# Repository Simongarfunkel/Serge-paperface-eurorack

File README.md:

# Serge Paperface → Eurorack

Modulfamilie: die Serge-Paperface-Module (73-75-Schaltungen) als Eurorack-Module.
Jedes Modul bekommt einen eigenen Ordner unter `modules/` mit Hardware-Revisionen, Panel und Dokumentation.
Gemeinsame Vorgaben stehen in [`docs/konventionen.md`](docs/konventionen.md).

## Module

| Modul | Ordner | Stand | Fertigungsfreigabe |
|---|---|---|---|
| Envelope | [`modules/envelope`](modules/envelope) | REV1: KiCad-Projekt komplett geroutet, ERC/DRC 0 Meldungen | nein – mechanische Prüfung und Prototyp offen |
| VCO (Oszillator) | [`modules/vco`](modules/vco) | REV1: KiCad-Schaltplan vollständig, Platine platziert, noch unverdrahtet, ERC/DRC offen | nein |
| Triple Waveshaper, Peak/Trough, Comparator, Dual Processor, Gate, Ring, Reverb, Preamp, Positive/Negative Slew | `modules/<modul>` | Originalauszüge abgelegt, noch kein KiCad | nein |

Neue Module: [`modules/_vorlage`](modules/_vorlage) kopieren und umbenennen. Bauteilwahl: [`docs/bauteilregel.md`](docs/bauteilregel.md). Gemeinsame KiCad-Bibliotheken: [`shared/kicad`](shared/kicad).

## Weitere Inhalte

- [`system/panel-layout`](system/panel-layout) – Gesamt-Panel-Layout (Vectorworks + PDF-Export).

## Lizenz

Noch nicht festgelegt. Die Schaltungen beruhen auf den Serge-73-75-Build-Unterlagen; deren Rechte liegen bei den
jeweiligen Urhebern. Auszüge aus den Originalunterlagen nicht ohne Klärung öffentlich stellen.
Fremdbibliotheken behalten ihre Lizenz (z. B. `LICENSE_AudioJacks.txt`, MIT, im Envelope-Projekt).

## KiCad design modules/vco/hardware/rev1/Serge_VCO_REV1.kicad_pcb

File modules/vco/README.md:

# VCO (Oszillator)

**Stand:** REV1 KiCad-Entwurf (22.10.2026), unverdrahtet, ERC/DRC offen · **Freigabe:** nein

## Dokumente

- [`docs/Serge_73-75_VCO_Originalauszug.pdf`](docs/Serge_73-75_VCO_Originalauszug.pdf) – Originalschaltung, BOM, Trimmanleitung.
- [`docs/Schaltplan_Original.png`](docs/Schaltplan_Original.png) – Originalschaltplan als Bild (300 dpi, gedreht).
- [`docs/Serge_VCO_Stabilisierung_Gruen.pdf`](docs/Serge_VCO_Stabilisierung_Gruen.pdf) – Stabilisierungsvorschlag (16.10.2026, Entwurf, keine freigegebene Nachbauschaltung).

## Original (Kurzfassung)

LM3900-Kern, 3 × 2N3904, 27-nF-Zeitkondensator, drei Trimmer:
1. Initial Offset – tiefste Frequenz, etwa 5–10 Hz
2. Range – Spanne bis etwa 10–14 kHz
3. Sinusformung im Saw-zu-Sinus-Waveshaper

## Geplante Änderungen (laut Vorschlag)

- Konkret: 27 nF als Folie oder C0G/NP0, 100 nF Entkopplung LM3900 Pin 14/7, kurze Timing-Schleife.
- Neu auszulegen: 1-V/Okt.-Eingang mit gepaartem NPN-Expo, Referenzstromregelung, Tempco, gepufferte Präzisionsreferenz.
- Ziel: fünf Oktaven, ±5 Cent nach Warmlaufen – noch nicht nachgewiesen.

## Revisionen

| Rev | Ordner | Inhalt | Status |
|---|---|---|---|
| REV1 | [`hardware/rev1`](hardware/rev1) | KiCad-Schaltplan (Label-Netzliste), Platine platziert, Stückliste, Netzliste | Entwurf – vor dem Öffnen [`BITTE_ZUERST_LESEN_REV1.txt`](hardware/rev1/BITTE_ZUERST_LESEN_REV1.txt) |

## Nächste Schritte

1. ERC in KiCad, Routing (Freerouting), DRC.
2. Abweichung SUM_P/SH_IN gegen Originalquelle prüfen (siehe BITTE_ZUERST_LESEN).
3. Originalkern aufbauen, Strom-/Spannungsbereiche und Reset-Zeit messen.

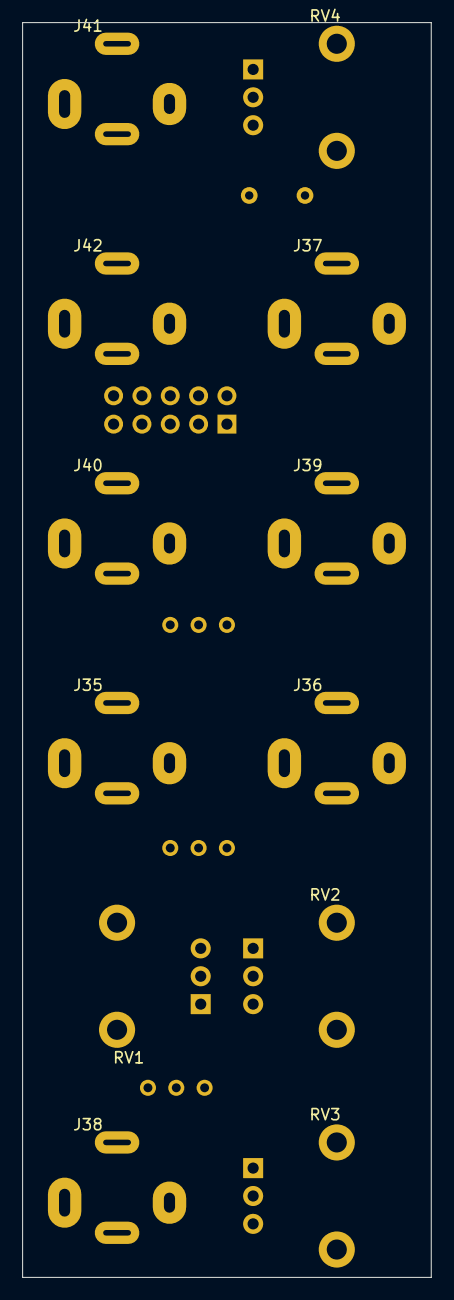
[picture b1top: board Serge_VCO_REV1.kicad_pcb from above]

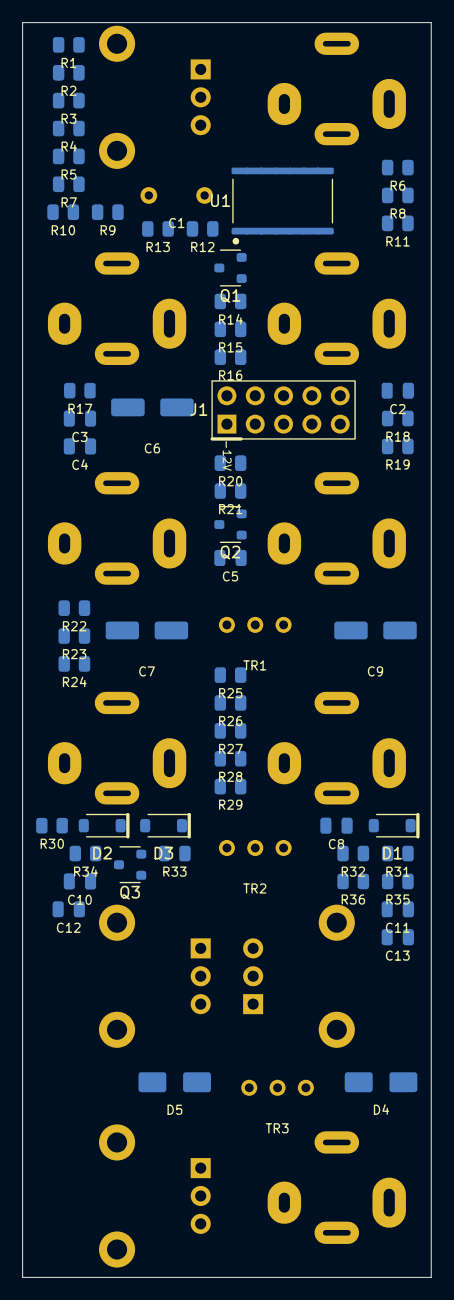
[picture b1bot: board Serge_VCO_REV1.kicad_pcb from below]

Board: 2 copper layers, 36.6 x 112.5 mm, 74 parts (62 on the bottom side), 46 nets, no tracks yet.

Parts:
C1: 27n Folie; C_Rect_L7.2mm_W2.5mm_P5.00mm
C2: 33p; C_0805_2012Metric
C3: 47p; C_0805_2012Metric
C4: 10n; C_0805_2012Metric
C5, C8: 82p; C_0805_2012Metric
C6, C9: 47u; CP_Elec_5x5.4
C7: 4u7; CP_Elec_5x5.4
C10, C11: 10u X7R; C_0805_2012Metric
C12, C13: 100n; C_0805_2012Metric
D1, D2, D3: 1N4148W; D_SOD-123
D4, D5: SS14; D_SMA
J1: EURORACK 10-PIN; PinHeader_2x05_P2.54mm_Vertical
J35: VC1 / PJ301BM; Jack_3.5mm_QingPu_WQP-PJ301BM_Vertical
J36: VC2 / PJ301BM; Jack_3.5mm_QingPu_WQP-PJ301BM_Vertical
J37: WAVE SHAPE CV / PJ301BM; Jack_3.5mm_QingPu_WQP-PJ301BM_Vertical
J38: SYNC / PJ301BM; Jack_3.5mm_QingPu_WQP-PJ301BM_Vertical
J39: SAW OUT / PJ301BM; Jack_3.5mm_QingPu_WQP-PJ301BM_Vertical
J40: SAW AC OUT / PJ301BM; Jack_3.5mm_QingPu_WQP-PJ301BM_Vertical
J41: SINE OUT / PJ301BM; Jack_3.5mm_QingPu_WQP-PJ301BM_Vertical
J42: SINE AC OUT / PJ301BM; Jack_3.5mm_QingPu_WQP-PJ301BM_Vertical
Q1, Q2, Q3: MMBT3904; SOT-23_EBC_MMBT3904
R1: 3M3; R_0805_2012Metric
R2, R3, R6, R7, R20, R28: 22k; R_0805_2012Metric
R4, R5, R8, R9, R25: 330k; R_0805_2012Metric
R10, R11: 1M; R_0805_2012Metric
R12: 15k; R_0805_2012Metric
R13, R15: 3k3; R_0805_2012Metric
R14: 15; R_0805_2012Metric
R16, R31: 33k; R_0805_2012Metric
R17, R26, R34: 1k; R_0805_2012Metric
R18: 82k; R_0805_2012Metric
R19: 4k7; R_0805_2012Metric
R21, R23, R33, R35: 330; R_0805_2012Metric
R22: 2k2; R_0805_2012Metric
R24, R36: 100k; R_0805_2012Metric
R27: 4M7; R_0805_2012Metric
R29, R30: 1M5; R_0805_2012Metric
R32: 10k; R_0805_2012Metric
RV1, RV2: 25k linear; Potentiometer_Alpha_RD901F-40-00D_Single_Vertical_CircularH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
RV3: 25k linear FREQ; Potentiometer_Alpha_RD901F-40-00D_Single_Vertical_CircularH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
RV4: 25k linear WAVE SHAPE; Potentiometer_Alpha_RD901F-40-00D_Single_Vertical_CircularH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
TR1: 25k OFFSET; Potentiometer_Bourns_3296W_Vertical
TR2: 25k RANGE; Potentiometer_Bourns_3296W_Vertical
TR3: 25k SINE; Potentiometer_Bourns_3296W_Vertical
U1: LM3900M (SOIC); SOIC-14_3.9x8.7mm_P1.27mm

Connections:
/+12V: D4.2, J1.9, J1.10
/-12V: D5.1, J1.1, J1.2
/CMP_FB: C2.2, R17.1
/CMP_N: C3.2, R18.2, R19.2
/CMP_OUT: R15.2, R17.2
/CMP_P: C2.1, R16.2
/CV1_A: R2.1, R4.1, RV1.1
/CV1_B: R3.1, R5.1, RV1.3
/CV1_TIP: J35.T, R1.2, RV1.2
/CV2_A: R6.1, R8.1, RV2.1
/CV2_B: R7.1, R9.1, RV2.3
/CV2_TIP: J36.T, RV2.2
/FREQ_W: R10.1, RV3.2
/GND: C10.2, C11.1, C12.2, C13.1, J1.3, J1.4, J1.5, J1.6, J1.7, J1.8, J35.S, J35.TN, J36.S, J36.TN, J37.S, J37.TN, J38.S, J38.TN, J39.S, J40.S, J41.S, J42.S, R2.2, R3.2, R6.2, R7.2, R20.2, R24.2, R28.2, R32.2, R34.2, R36.2, RV3.1, RV4.1, TR1.1, TR3.3
/INT_N: C1.1, Q1.2
/NODE_X: R12.2, R13.2
/OFS_W: R11.1, TR1.2
/Q1_C: Q1.3, R15.1
/Q1_E: Q1.1, R14.1
/Q2_B: Q2.2, R21.2
/Q3_B: Q3.2, R33.2
/RANGE_W: C5.1, TR2.2
/SAW: C1.2, C3.1, R14.2, R16.1, R21.1
/SAW_AC: C6.2, J40.T, R24.1
/SAW_BUF: Q2.1, R22.1, R23.1, TR2.1, TR3.1
/SAW_OUT: C6.1, J39.T, R23.2
/SH_FB: C8.2, D2.2, R31.2, R32.1
/SH_IN: D3.2, R25.2, R27.2, R29.2
/SH_N: C8.1, D2.1, D3.1, R30.1
/SH_OUT: R30.2, R31.1, R33.1
/SINE_AC: C9.2, J42.T, R36.1
/SINE_AC_IN: C7.1, R25.1
/SINE_BUF: Q3.1, R34.1, R35.1
/SINE_OUT: C9.1, J41.T, R35.2
/SINE_W: C7.2, TR3.2
/SUM_N: R4.2, R8.2, R10.2, R12.1, U1.6
/SUM_P: C5.2, R5.2, R9.2, R11.2, U1.1
/SYNC_AC: C4.2, R19.1
/SYNC_IN: C4.1, J38.T, R20.1
/U1A_OUT: R13.1, U1.5
/V+: C10.1, C12.1, D4.1, Q2.3, Q3.3, R1.1, R18.1, R26.1, RV3.3, TR1.3
/V-: C11.2, C13.2, D5.2, R22.2, TR2.3
/WS_D: D1.1, R29.1
/WS_IN: D1.2, J37.T, R28.1
/WS_TOP: R26.2, RV4.3
/WS_W: R27.1, RV4.2

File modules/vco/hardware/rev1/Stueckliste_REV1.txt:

Serge VCO REV1 - Stueckliste (abgeleitet aus dem Schaltplan)
Ref	Wert	Footprint	Ausfuehrung
C1	27n Folie	C_Rect_L7.2mm_W2.5mm_P5.00mm	THT
C2	33p	C_0805_2012Metric	SMD
C3	47p	C_0805_2012Metric	SMD
C4	10n	C_0805_2012Metric	SMD
C5	82p	C_0805_2012Metric	SMD
C6	47u	CP_Elec_5x5.4	SMD
C7	4u7	CP_Elec_5x5.4	SMD
C8	82p	C_0805_2012Metric	SMD
C9	47u	CP_Elec_5x5.4	SMD
C10	10u X7R	C_0805_2012Metric	SMD
C11	10u X7R	C_0805_2012Metric	SMD
C12	100n	C_0805_2012Metric	SMD
C13	100n	C_0805_2012Metric	SMD
D1	1N4148W	D_SOD-123	SMD
D2	1N4148W	D_SOD-123	SMD
D3	1N4148W	D_SOD-123	SMD
D4	SS14	D_SMA	SMD
D5	SS14	D_SMA	SMD
J1	EURORACK 10-PIN	PinHeader_2x05_P2.54mm_Vertical	THT
J35	VC1 / PJ301BM	Jack_3.5mm_QingPu_WQP-PJ301BM_Vertical	THT
J36	VC2 / PJ301BM	Jack_3.5mm_QingPu_WQP-PJ301BM_Vertical	THT
J37	WAVE SHAPE CV / PJ301BM	Jack_3.5mm_QingPu_WQP-PJ301BM_Vertical	THT
J38	SYNC / PJ301BM	Jack_3.5mm_QingPu_WQP-PJ301BM_Vertical	THT
J39	SAW OUT / PJ301BM	Jack_3.5mm_QingPu_WQP-PJ301BM_Vertical	THT
J40	SAW AC OUT / PJ301BM	Jack_3.5mm_QingPu_WQP-PJ301BM_Vertical	THT
J41	SINE OUT / PJ301BM	Jack_3.5mm_QingPu_WQP-PJ301BM_Vertical	THT
J42	SINE AC OUT / PJ301BM	Jack_3.5mm_QingPu_WQP-PJ301BM_Vertical	THT
Q1	MMBT3904	SOT-23_EBC_MMBT3904	SMD
Q2	MMBT3904	SOT-23_EBC_MMBT3904	SMD
Q3	MMBT3904	SOT-23_EBC_MMBT3904	SMD
R1	3M3	R_0805_2012Metric	SMD
R2	22k	R_0805_2012Metric	SMD
R3	22k	R_0805_2012Metric	SMD
R4	330k	R_0805_2012Metric	SMD
R5	330k	R_0805_2012Metric	SMD
R6	22k	R_0805_2012Metric	SMD
R7	22k	R_0805_2012Metric	SMD
R8	330k	R_0805_2012Metric	SMD
R9	330k	R_0805_2012Metric	SMD
R10	1M	R_0805_2012Metric	SMD
R11	1M	R_0805_2012Metric	SMD
R12	15k	R_0805_2012Metric	SMD
R13	3k3	R_0805_2012Metric	SMD
R14	15	R_0805_2012Metric	SMD
R15	3k3	R_0805_2012Metric	SMD
R16	33k	R_0805_2012Metric	SMD
R17	1k	R_0805_2012Metric	SMD
R18	82k	R_0805_2012Metric	SMD
R19	4k7	R_0805_2012Metric	SMD
R20	22k	R_0805_2012Metric	SMD
R21	330	R_0805_2012Metric	SMD
R22	2k2	R_0805_2012Metric	SMD
R23	330	R_0805_2012Metric	SMD
R24	100k	R_0805_2012Metric	SMD
R25	330k	R_0805_2012Metric	SMD
R26	1k	R_0805_2012Metric	SMD
R27	4M7	R_0805_2012Metric	SMD
R28	22k	R_0805_2012Metric	SMD
R29	1M5	R_0805_2012Metric	SMD
R30	1M5	R_0805_2012Metric	SMD
R31	33k	R_0805_2012Metric	SMD
R32	10k	R_0805_2012Metric	SMD
R33	330	R_0805_2012Metric	SMD
R34	1k	R_0805_2012Metric	SMD
R35	330	R_0805_2012Metric	SMD
R36	100k	R_0805_2012Metric	SMD
RV1	25k linear	Potentiometer_Alpha_RD901F-40-00D_Single_Vertical_CircularHoles	THT
RV2	25k linear	Potentiometer_Alpha_RD901F-40-00D_Single_Vertical_CircularHoles	THT
RV3	25k linear FREQ	Potentiometer_Alpha_RD901F-40-00D_Single_Vertical_CircularHoles	THT
RV4	25k linear WAVE SHAPE	Potentiometer_Alpha_RD901F-40-00D_Single_Vertical_CircularHoles	THT
TR1	25k OFFSET	Potentiometer_Bourns_3296W_Vertical	THT
TR2	25k RANGE	Potentiometer_Bourns_3296W_Vertical	THT
TR3	25k SINE	Potentiometer_Bourns_3296W_Vertical	THT
U1	LM3900M (SOIC)	SOIC-14_3.9x8.7mm_P1.27mm	SMD

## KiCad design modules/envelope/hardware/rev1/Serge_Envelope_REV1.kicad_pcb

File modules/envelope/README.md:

# Envelope

**Stand:** REV1 elektrisch geprüft (12.10.2026) · **Freigabe:** nein

Vor dem Öffnen: [`hardware/rev1/BITTE_ZUERST_LESEN_REV1.txt`](hardware/rev1/BITTE_ZUERST_LESEN_REV1.txt).

## Revisionen

| Rev | Ordner | Inhalt | Status |
|---|---|---|---|
| REV0 | [`panel/rev0`](panel/rev0) | Original-Panel-DXF, Zeichnungsreferenz, Bilder | **zurückgezogen** – fehlerhafte Angabe zum Stromanschluss; DXF bleibt Panelreferenz |
| REV1 | [`hardware/rev1`](hardware/rev1) | KiCad-Projekt, Gerber, Stückliste, ERC/DRC, Netzabgleich | elektrisch geprüft |

## REV1 in Kürze

- Vollständige Übertragung der 73-75-Envelope-Schaltung, 114 Footprints, beidseitig bestückt.
- Eigener +6-V-Regler aus +12 V, LED-Treiber, isolierte Cycle-Umschaltung, 10-Pin-Eurorack.
- ERC 0, DRC 0, 0 unverbundene Pads, Schaltplan/PCB-Parität 0 Abweichungen.

## Offene Punkte vor Fertigung

- SW1: konkretes Schaltermodell und Bauhöhe bestätigen (Footprint ist generischer Entwurf).
- Mechanischer Gesamtaufbau: Paneldicke, Rackschienenfreiraum, PCB-Umriss 77,28 × 112,5 mm.
- LED-Bohrung (3 mm angenommen; 2,5-mm-Zeichen in der DXF ist nur Positionsmarke).
- Zeitkondensator, Elkos, Trimmer und Teilenummern gegen Datenblätter abgleichen.
- Prototyp: +6 V an TP3 einstellen, Abgleich an TP7, Poti-Wirkrichtung und CV-/Trigger-Funktionen prüfen.

## Quellen

- [`docs/Serge_73-75_Envelope_Originalauszug.pdf`](docs/Serge_73-75_Envelope_Originalauszug.pdf), [`docs/Schaltplan_Original.png`](docs/Schaltplan_Original.png)

73-75 Build Instructions, S. 32–34; Originalpanel `ENVELOPE_REV.0.dxf`. Weitere im Readme der REV1.

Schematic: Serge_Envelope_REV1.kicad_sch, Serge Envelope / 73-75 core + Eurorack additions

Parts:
C1: 10n; C_0805_2012Metric
C2: 220p; C_0805_2012Metric
C3: 470n; C_Rect_L7.2mm_W2.5mm_P5.00mm
C4: 33p; C_0805_2012Metric
C5: 100p; C_0805_2012Metric
C6, C7, C8, C9: 100n; C_0805_2012Metric
C10, C11: 10u; CP_Elec_5x5.4
C12: 47u; CP_Elec_5x5.4
D1, D2, D3, D4, D5, D6: 1N4148; D_DO-35_SOD27_P7.62mm_Horizontal
D7: SS14; D_SMA
D8: 1N4007; D_DO-41_SOD81_P10.16mm_Horizontal
D9, D10: BAT85; D_DO-35_SOD27_P7.62mm_Horizontal
J1: END / PJ301BM; Jack_3.5mm_QingPu_WQP-PJ301BM_Vertical
J2, J5: ENV_OUT / PJ301BM; Jack_3.5mm_QingPu_WQP-PJ301BM_Vertical
J3: WINDOW_OUT / PJ301BM; Jack_3.5mm_QingPu_WQP-PJ301BM_Vertical
J4: START / PJ301BM; Jack_3.5mm_QingPu_WQP-PJ301BM_Vertical
J6: CYCLE / PJ301BM; Jack_3.5mm_QingPu_WQP-PJ301BM_Vertical
J7: HOLD / PJ301BM; Jack_3.5mm_QingPu_WQP-PJ301BM_Vertical
J8: WINDOW_CV / PJ301BM; Jack_3.5mm_QingPu_WQP-PJ301BM_Vertical
J9: DURATION_CV / PJ301BM; Jack_3.5mm_QingPu_WQP-PJ301BM_Vertical
J10: EURORACK 10 PIN; IDC-Header_2x05_P2.54mm_Vertical
LED1: RED FLAT TOP 3mm; LED_D3.0mm
Q1, Q2, Q3, Q4, Q5, Q6: 2N3904; TO-92_Inline
Q7, Q8, Q9: 2N3906; TO-92_Inline
Q10: BC547; TO-92_Inline
R1, R7, R13, R40, R46: 470; R_0805_2012Metric
R2, R4, R5, R19, R45, R49, R50, R52: 100k; R_0805_2012Metric
R3, R10, R25, R29, R30, R31, R43: 33k; R_0805_2012Metric
R6, R32: 82k; R_0805_2012Metric
R8, R44: 1M5; R_0805_2012Metric
R9, R22, R23, R24, R26, R27, R35: 470k; R_0805_2012Metric
R11, R37: 6k8; R_0805_2012Metric
R12: 33; R_0805_2012Metric
R14, R17: 10M; R_0805_2012Metric
R15, R16: 68k; R_0805_2012Metric
R18: 15k; R_0805_2012Metric
R20, R21: 22k; R_0805_2012Metric
R28: 3k3; R_0805_2012Metric
R33, R34: 330k; R_0805_2012Metric
R36, R38: 1k; R_0805_2012Metric
R39: 2k2; R_0805_2012Metric
R41, R42: 1M; R_0805_2012Metric
R47: 110; R_0805_2012Metric
R48: 360; R_0805_2012Metric
R51: 4k7; R_0805_2012Metric
RV1, RV2, RV3, RV4: 25k linear; Potentiometer_Alpha_RD901F-40-00D_Single_Vertical_CircularH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
SW1: MINI PRINT ON-OFF; MiniToggle_SPDT_P4.7_REVIEW
TP1: GND; TestPoint_Pad_D1.5mm
TP2: +12V; TestPoint_Pad_D1.5mm
TP3: +6V; TestPoint_Pad_D1.5mm
TP4: ENV_INTERNAL; TestPoint_Pad_D1.5mm
TP5: END_INTERNAL; TestPoint_Pad_D1.5mm
TP6: WINDOW_RAW; TestPoint_Pad_D1.5mm
TP7: ENV_CORE; TestPoint_Pad_D1.5mm
TP8: RAW_ENV_TEST; TestPoint_Pad_D1.5mm
TR1: 10k; Potentiometer_Bourns_3296W_Vertical
TR2: 25k; Potentiometer_Bourns_3296W_Vertical
TR3: 100; Potentiometer_Bourns_3296W_Vertical
U1, U2: LM3900; DIP-14_W7.62mm
U3: LM317T; TO-220-3_Horizontal_TabDown

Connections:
/+6V: C9.1, C11.1, D8.2 (A), Q7.1 (E), Q8.1 (E), R8.1, R9.1, R47.1, RV4.1, SW1.2 (B), TP3.1, U3.2 (VO)
/+12V: C6.1, C7.1, C8.1, C10.1, C12.1, D7.1 (K), D8.1 (K), Q5.3 (C), Q9.1 (E), R11.1, R32.1, R35.1, R51.1, TP2.1, TR2.3, U1.14 (VCC), U2.14 (VCC), U3.3 (VI)
/+12V_RAW: D7.2 (A), J10.9, J10.10
/CYCLE: D9.2 (A), J6.T (TIP), R52.1
/CYCLE_OR: D9.1 (K), D10.1 (K), R1.1
/CYCLE_SWITCHED: D10.2 (A), SW1.3 (C)
/DURATION_CV: J9.T (TIP), RV3.2
/DUR_LEFT: R20.1, R24.1, RV2.3, RV3.1
/DUR_RIGHT: R21.1, R26.1, RV3.3
/END: J1.T (TIP), R7.2
/END_INTERNAL: D1.1 (K), R6.1, R7.1, TP5.1, U1.5 (OUT)
/END_MINUS: R6.2, U1.6 (-)
/END_PLUS: R5.2, U1.1 (+)
/ENV_BUF_MINUS: R33.2, R34.2, U1.11 (-)
/ENV_BUF_PLUS: R35.2, U1.12 (+)
/ENV_CORE: C3.2, D5.1 (K), R12.2, R13.1, R33.1, R44.1, TP7.1, U2.10 (OUT)
/ENV_DRV: Q9.3 (C), R38.2, R40.1
/ENV_EMITTER: Q6.1 (E), R38.1, R39.1
/ENV_INTERNAL: D6.1 (K), R5.1, R18.1, R49.1, TP4.1, U1.10 (OUT)
/ENV_OUT: J2.T (TIP), J5.T (TIP), R40.2
/ENV_SENSE: Q5.1 (E), R34.1, R36.1
/FALL_TOP: Q8.3 (C), RV2.1
/FALL_W: R23.1, RV2.2
/GND: C6.2, C7.2, C8.2, C9.2, C10.2, C11.2, C12.2, J1.S (SLEEVE), J2.S (SLEEVE), J3.S (SLEEVE), J4.S (SLEEVE), J5.S (SLEEVE), J6.S (SLEEVE), J7.S (SLEEVE), J8.S (SLEEVE), J9.S (SLEEVE), J10.3, J10.4, J10.5, J10.6, J10.7, J10.8, Q1.1 (E), Q3.1 (E), Q4.1 (E), Q10.3 (E), R2.2, R3.2, R15.2, R16.2, R19.2, R20.2, R21.2, R30.2, R37.2, R39.2, R43.2, R50.2, R52.2, RV1.3, RV4.3, TP1.1, TR2.1, TR3.2, TR3.3, U1.7 (GND), U2.2 (+), U2.7 (GND), U2.13 (+)
/HOLD: J7.T (TIP), R29.1, R30.1
/HOLD_BASE: Q3.2 (B), Q4.3 (C), R29.2
/INT_MINUS: C3.1, Q2.1 (E), R17.2, U2.11 (-)
/INT_PLUS: Q3.3 (C), R25.1, R28.2, U2.12 (+)
/LATCH_D_ANODE: C2.1, D3.2 (A), R9.2
/LATCH_MINUS: D2.1 (K), R8.2, U1.3 (-)
/LATCH_OUT: C2.2, D4.1 (K), R10.1, U1.4 (OUT)
/LATCH_PLUS: D3.1 (K), U1.2 (+)
/LED_ANODE: LED1.2 (A), R51.2
/LED_BASE: Q10.2 (B), R49.2, R50.1
/LED_CATHODE: LED1.1 (K), Q10.1 (C)
/NULL_LEFT: R14.2, R15.1, TR1.3
/NULL_MINUS: R14.1, U2.8 (-)
/NULL_OUT: TR1.2, U2.9 (OUT)
/NULL_RIGHT: R16.1, R17.1, TR1.1
/Q1_BASE: Q1.2 (B), R10.2
/Q1_COL: Q1.3 (C), Q2.2 (B), R11.2
/Q2_COL: Q2.3 (C), R12.1
/Q6_BASE: Q6.2 (B), R36.2, R37.1
/Q9_BASE: Q6.3 (C), Q9.2 (B)
/RANGE_W: R27.1, TR2.2
/RATE_BASE: Q7.2 (B), Q8.2 (B), R18.2, R19.1
/RATE_MINUS: R22.2, R23.2, R24.2, R25.2, U1.8 (-)
/RATE_OUT: R28.1, U1.9 (OUT)
/RATE_PLUS: R26.2, R27.2, U1.13 (+)
/RAW_ENV_TEST: R13.2, TP8.1
/REG_ADJ: R47.2, R48.1, U3.1 (ADJ)
/REG_TRIM: R48.2, TR3.1
/RISE_TOP: Q7.3 (C), RV1.1
/RISE_W: R22.1, RV1.2
/START: C1.1, J4.T (TIP), R2.1
/THRESH_BUS: D4.2 (A), D5.2 (A), D6.2 (A), Q5.2 (B), R32.2
/TRIG_D: D1.2 (A), D2.2 (A), R4.2
/TRIG_NODE: C1.2, R1.2, R3.1, R4.1
/WINDOW_BUFFER: C5.2, R46.1, U2.4 (OUT)
/WINDOW_BUF_MINUS: R45.2, U2.3 (-)
/WINDOW_CV: J8.T (TIP), R42.1, R43.1
/WINDOW_HOLD_BASE: Q4.2 (B), R31.2
/WINDOW_MINUS: C4.1, C5.1, R44.2, U2.6 (-)
/WINDOW_OUT: J3.T (TIP), R46.2
/WINDOW_PLUS: R41.2, R42.2, U2.1 (+)
/WINDOW_RAW: C4.2, R31.1, R45.1, TP6.1, U2.5 (OUT)
/WINDOW_W: R41.1, RV4.2

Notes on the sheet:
START / END / LATCH
INTEGRATOR / HOLD NULL
RISE / FALL / DURATION
ENVELOPE BUFFER
WINDOW
POWER / +6V REGULATOR
LED / CYCLE
PANEL JACKS
TEST POINTS
REVIEW REV1 - electrically connected source transcription; PCB routing and mechanics pending verification

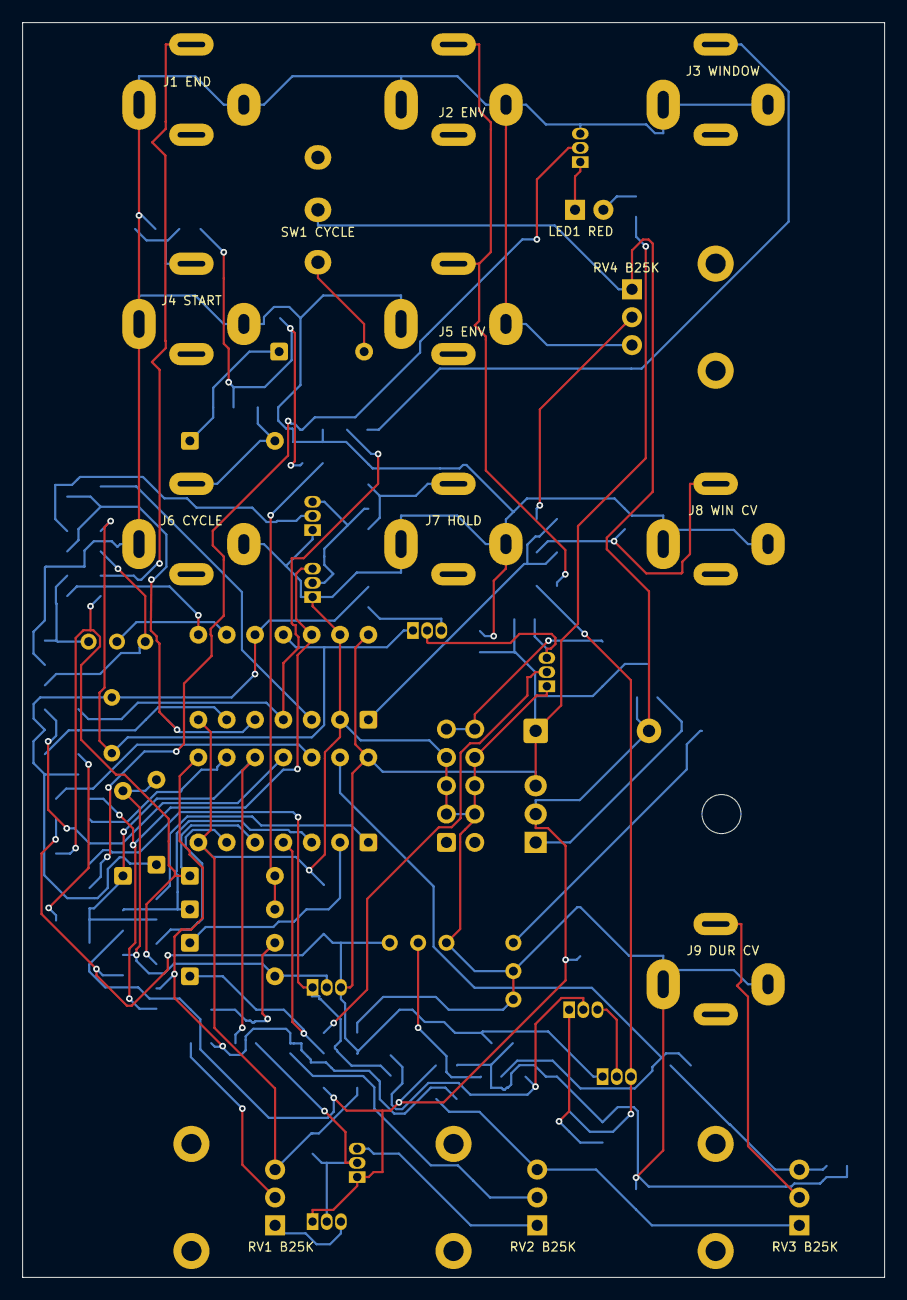
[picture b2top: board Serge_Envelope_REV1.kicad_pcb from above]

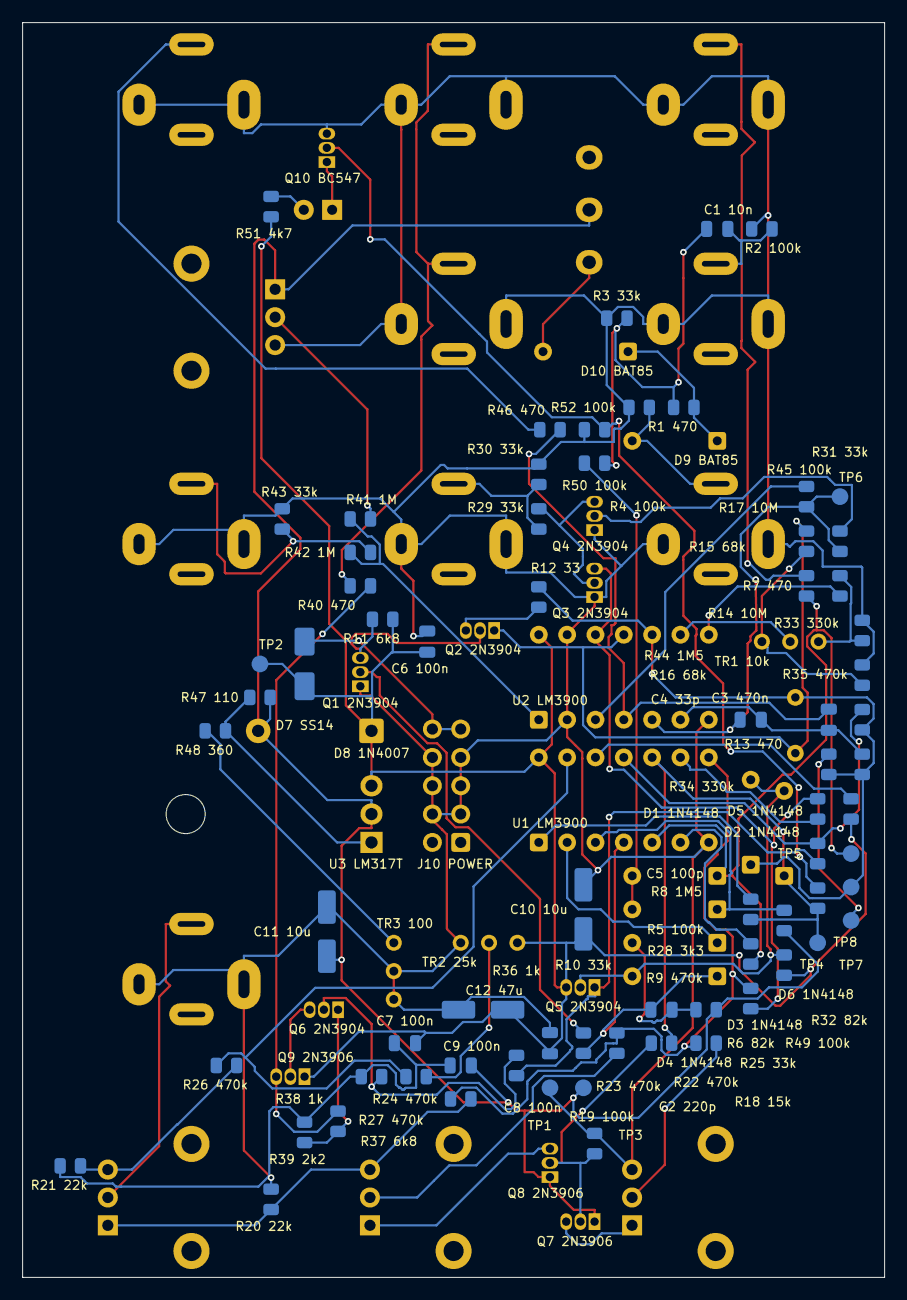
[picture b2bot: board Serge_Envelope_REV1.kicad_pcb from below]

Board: 2 copper layers, 77.3 x 112.5 mm, 114 parts (99 on the bottom side), 67 nets.

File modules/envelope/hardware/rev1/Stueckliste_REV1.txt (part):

SERGE ENVELOPE REV1 - STUECKLISTE
Stand: 12.10.2026
Status: Elektrisches Pruefprojekt, keine mechanische/Hardware-Freigabe. REV0-Refdes sind zurueckgezogen.

C1 | 10n | Serge_Local:C_0805_2012Metric | START / END / LATCH
C2 | 220p | Serge_Local:C_0805_2012Metric | START / END / LATCH
C3 | 470n | Serge_Local:C_Rect_L7.2mm_W2.5mm_P5.00mm | INTEGRATOR / HOLD NULL
C4 | 33p | Serge_Local:C_0805_2012Metric | WINDOW
C5 | 100p | Serge_Local:C_0805_2012Metric | WINDOW
C6 | 100n | Serge_Local:C_0805_2012Metric | POWER / +6V REGULATOR
C7 | 100n | Serge_Local:C_0805_2012Metric | POWER / +6V REGULATOR
C8 | 100n | Serge_Local:C_0805_2012Metric | POWER / +6V REGULATOR
C9 | 100n | Serge_Local:C_0805_2012Metric | POWER / +6V REGULATOR
C10 | 10u | Serge_Local:CP_Elec_5x5.4 | POWER / +6V REGULATOR
C11 | 10u | Serge_Local:CP_Elec_5x5.4 | POWER / +6V REGULATOR
C12 | 47u | Serge_Local:CP_Elec_5x5.4 | POWER / +6V REGULATOR
D1 | 1N4148 | Serge_Local:D_DO-35_SOD27_P7.62mm_Horizontal | START / END / LATCH
D2 | 1N4148 | Serge_Local:D_DO-35_SOD27_P7.62mm_Horizontal | START / END / LATCH
D3 | 1N4148 | Serge_Local:D_DO-35_SOD27_P7.62mm_Horizontal | START / END / LATCH
D4 | 1N4148 | Serge_Local:D_DO-35_SOD27_P7.62mm_Horizontal | ENVELOPE BUFFER
D5 | 1N4148 | Serge_Local:D_DO-35_SOD27_P7.62mm_Horizontal | ENVELOPE BUFFER
D6 | 1N4148 | Serge_Local:D_DO-35_SOD27_P7.62mm_Horizontal | ENVELOPE BUFFER
D7 | SS14 | Serge_Local:D_SMA | POWER / +6V REGULATOR
D8 | 1N4007 | Serge_Local:D_DO-41_SOD81_P10.16mm_Horizontal | POWER / +6V REGULATOR
D9 | BAT85 | Serge_Local:D_DO-35_SOD27_P7.62mm_Horizontal | LED / CYCLE
D10 | BAT85 | Serge_Local:D_DO-35_SOD27_P7.62mm_Horizontal | LED / CYCLE
J1 | END / PJ301BM | Serge_Local:Jack_3.5mm_QingPu_WQP-PJ301BM_Vertical | PANEL JACKS
J2 | ENV_OUT / PJ301BM | Serge_Local:Jack_3.5mm_QingPu_WQP-PJ301BM_Vertical | PANEL JACKS
J3 | WINDOW_OUT / PJ301BM | Serge_Local:Jack_3.5mm_QingPu_WQP-PJ301BM_Vertical | PANEL JACKS
J4 | START / PJ301BM | Serge_Local:Jack_3.5mm_QingPu_WQP-PJ301BM_Vertical | PANEL JACKS
J5 | ENV_OUT / PJ301BM | Serge_Local:Jack_3.5mm_QingPu_WQP-PJ301BM_Vertical | PANEL JACKS
J6 | CYCLE / PJ301BM | Serge_Local:Jack_3.5mm_QingPu_WQP-PJ301BM_Vertical | PANEL JACKS
J7 | HOLD / PJ301BM | Serge_Local:Jack_3.5mm_QingPu_WQP-PJ301BM_Vertical | PANEL JACKS
J8 | WINDOW_CV / PJ301BM | Serge_Local:Jack_3.5mm_QingPu_WQP-PJ301BM_Vertical | PANEL JACKS
J9 | DURATION_CV / PJ301BM | Serge_Local:Jack_3.5mm_QingPu_WQP-PJ301BM_Vertical | PANEL JACKS
J10 | EURORACK 10 PIN | Serge_Local:IDC-Header_2x05_P2.54mm_Vertical | POWER / +6V REGULATOR
LED1 | RED FLAT TOP 3mm | Serge_Local:LED_D3.0mm | LED / CYCLE
Q1 | 2N3904 | Serge_Local:TO-92_Inline | START / END / LATCH
Q2 | 2N3904 | Serge_Local:TO-92_Inline | INTEGRATOR / HOLD NULL
Q3 | 2N3904 | Serge_Local:TO-92_Inline | RISE / FALL / DURATION
Q4 | 2N3904 | Serge_Local:TO-92_Inline | RISE / FALL / DURATION
Q5 | 2N3904 | Serge_Local:TO-92_Inline | ENVELOPE BUFFER
Q6 | 2N3904 | Serge_Local:TO-92_Inline | ENVELOPE BUFFER
Q7 | 2N3906 | Serge_Local:TO-92_Inline | RISE / FALL / DURATION
Q8 | 2N3906 | Serge_Local:TO-92_Inline | RISE / FALL / DURATION
Q9 | 2N3906 | Serge_Local:TO-92_Inline | ENVELOPE BUFFER
Q10 | BC547 | Serge_Local:TO-92_Inline | LED / CYCLE
R1 | 470 | Serge_Local:R_0805_2012Metric | START / END / LATCH
R2 | 100k | Serge_Local:R_0805_2012Metric | START / END / LATCH
R3 | 33k | Serge_Local:R_0805_2012Metric | START / END / LATCH
R4 | 100k | Serge_Local:R_0805_2012Metric | START / END / LATCH
R5 | 100k | Serge_Local:R_0805_2012Metric | START / END / LATCH
R6 | 82k | Serge_Local:R_0805_2012Metric | START / END / LATCH
R7 | 470 | Serge_Local:R_0805_2012Metric | START / END / LATCH
R8 | 1M5 | Serge_Local:R_0805_2012Metric | START / END / LATCH
R9 | 470k | Serge_Local:R_0805_2012Metric | START / END / LATCH
R10 | 33k | Serge_Local:R_0805_2012Metric | START / END / LATCH
R11 | 6k8 | Serge_Local:R_0805_2012Metric | START / END / LATCH
R12 | 33 | Serge_Local:R_0805_2012Metric | INTEGRATOR / HOLD NULL
R13 | 470 | Serge_Local:R_0805_2012Metric | INTEGRATOR / HOLD NULL
R14 | 10M | Serge_Local:R_0805_2012Metric | INTEGRATOR / HOLD NULL
R15 | 68k | Serge_Local:R_0805_2012Metric | INTEGRATOR / HOLD NULL
R16 | 68k | Serge_Local:R_0805_2012Metric | INTEGRATOR / HOLD NULL
R17 | 10M | Serge_Local:R_0805_2012Metric | INTEGRATOR / HOLD NULL
R18 | 15k | Serge_Local:R_0805_2012Metric | RISE / FALL / DURATION
R19 | 100k | Serge_Local:R_0805_2012Metric | RISE / FALL / DURATION
R20 | 22k | Serge_Local:R_0805_2012Metric | RISE / FALL / DURATION
R21 | 22k | Serge_Local:R_0805_2012Metric | RISE / FALL / DURATION
R22 | 470k | Serge_Local:R_0805_2012Metric | RISE / FALL / DURATION
R23 | 470k | Serge_Local:R_0805_2012Metric | RISE / FALL / DURATION
R24 | 470k | Serge_Local:R_0805_2012Metric | RISE / FALL / DURATION
R25 | 33k | Serge_Local:R_0805_2012Metric | RISE / FALL / DURATION
R26 | 470k | Serge_Local:R_0805_2012Metric | RISE / FALL / DURATION
R27 | 470k | Serge_Local:R_0805_2012Metric | RISE / FALL / DURATION
R28 | 3k3 | Serge_Local:R_0805_2012Metric | RISE / FALL / DURATION
R29 | 33k | Serge_Local:R_0805_2012Metric | RISE / FALL / DURATION
R30 | 33k | Serge_Local:R_0805_2012Metric | RISE / FALL / DURATION
R31 | 33k | Serge_Local:R_0805_2012Metric | RISE / FALL / DURATION
R32 | 82k | Serge_Local:R_0805_2012Metric | ENVELOPE BUFFER
R33 | 330k | Serge_Local:R_0805_2012Metric | ENVELOPE BUFFER
R34 | 330k | Serge_Local:R_0805_2012Metric | ENVELOPE BUFFER
R35 | 470k | Serge_Local:R_0805_2012Metric | ENVELOPE BUFFER
R36 | 1k | Serge_Local:R_0805_2012Metric | ENVELOPE BUFFER
R37 | 6k8 | Serge_Local:R_0805_2012Metric | ENVELOPE BUFFER
R38 | 1k | Serge_Local:R_0805_2012Metric | ENVELOPE BUFFER
R39 | 2k2 | Serge_Local:R_0805_2012Metric | ENVELOPE BUFFER
R40 | 470 | Serge_Local:R_0805_2012Metric | ENVELOPE BUFFER
R41 | 1M | Serge_Local:R_0805_2012Metric | WINDOW
R42 | 1M | Serge_Local:R_0805_2012Metric | WINDOW
R43 | 33k | Serge_Local:R_0805_2012Metric | WINDOW
R44 | 1M5 | Serge_Local:R_0805_2012Metric | WINDOW
R45 | 100k | Serge_Local:R_0805_2012Metric | WINDOW
R46 | 470 | Serge_Local:R_0805_2012Metric | WINDOW
R47 | 110 | Serge_Local:R_0805_2012Metric | POWER / +6V REGULATOR
R48 | 360 | Serge_Local:R_0805_2012Metric | POWER / +6V REGULATOR
R49 | 100k | Serge_Local:R_0805_2012Metric | LED / CYCLE
R50 | 100k | Serge_Local:R_0805_2012Metric | LED / CYCLE
R51 | 4k7 | Serge_Local:R_0805_2012Metric | LED / CYCLE
R52 | 100k | Serge_Local:R_0805_2012Metric | LED / CYCLE
RV1 | 25k linear | Serge_Local:Potentiometer_Alpha_RD901F-40-00D_Single_Vertical_CircularHoles | RISE / FALL / DURATION
RV2 | 25k linear | Serge_Local:Potentiometer_Alpha_RD901F-40-00D_Single_Vertical_CircularHoles | RISE / FALL / DURATION
RV3 | 25k linear | Serge_Local:Potentiometer_Alpha_RD901F-40-00D_Single_Vertical_CircularHoles | RISE / FALL / DURATION
RV4 | 25k linear | Serge_Local:Potentiometer_Alpha_RD901F-40-00D_Single_Vertical_CircularHoles | WINDOW
SW1 | MINI PRINT ON-OFF | Serge_Local:MiniToggle_SPDT_P4.7_REVIEW | LED / CYCLE
TP1 | GND | Serge_Local:TestPoint_Pad_D1.5mm | TEST POINTS
TP2 | +12V | Serge_Local:TestPoint_Pad_D1.5mm | TEST POINTS
TP3 | +6V | Serge_Local:TestPoint_Pad_D1.5mm | TEST POINTS
TP4 | ENV_INTERNAL | Serge_Local:TestPoint_Pad_D1.5mm | TEST POINTS
TP5 | END_INTERNAL | Serge_Local:TestPoint_Pad_D1.5mm | TEST POINTS
TP6 | WINDOW_RAW | Serge_Local:TestPoint_Pad_D1.5mm | TEST POINTS
TP7 | ENV_CORE | Serge_Local:TestPoint_Pad_D1.5mm | TEST POINTS
TP8 | RAW_ENV_TEST | Serge_Local:TestPoint_Pad_D1.5mm | TEST POINTS
TR1 | 10k | Serge_Local:Potentiometer_Bourns_3296W_Vertical | INTEGRATOR / HOLD NULL
TR2 | 25k | Serge_Local:Potentiometer_Bourns_3296W_Vertical | RISE / FALL / DURATION
TR3 | 100 | Serge_Local:Potentiometer_Bourns_3296W_Vertical | POWER / +6V REGULATOR
U1 | LM3900 | Serge_Local:DIP-14_W7.62mm | START / END / LATCH
U2 | LM3900 | Serge_Local:DIP-14_W7.62mm | INTEGRATOR / HOLD NULL
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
